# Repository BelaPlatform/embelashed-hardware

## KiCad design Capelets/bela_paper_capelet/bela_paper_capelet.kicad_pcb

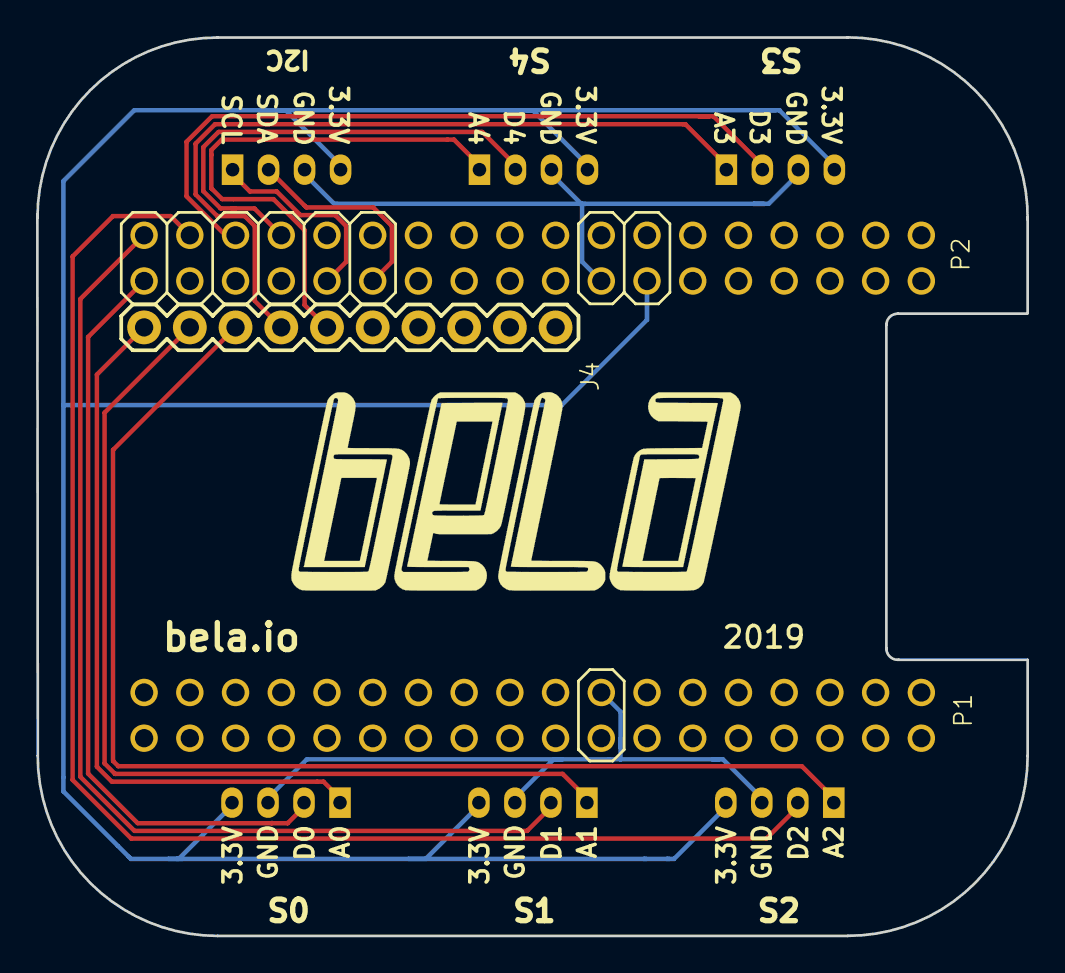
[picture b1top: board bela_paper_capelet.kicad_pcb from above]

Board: 2 copper layers, 55.0 x 49.9 mm, 9 parts (0 on the bottom side), 14 nets.

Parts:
J1, J2, J3, J5, J6, J7: Grove_4x2mm; JST_PH_S4B-PH-K_04x2.00mm_Angled
J4: M10SILK_FEMALE_PTH; 1X10
P1: PINHD-2X18; 2X18_P1
P2: PINHD-2X18; 2X18_P2

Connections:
+3V3: J1.4, J2.4, J3.4, J5.4, J6.4, J7.4
/A0: J4.10, J5.1
/A1: J4.9, J6.1
/A2: J4.8, J7.1
/A3: J3.1, J4.7
/A4: J2.1, J4.6
/D0: J5.2, P2.1
/D1: J6.2, P2.2
/D2: J7.2, P2.4
/D3: J3.2, P2.6
/D4: J2.2, P2.8
/SCL: J1.1, P2.9
/SDA: J1.2, P2.11
GND: J1.3, J2.3, J3.3, J4.2, J5.3, J6.3, J7.3, P1.16, P1.22, P2.15, P2.21

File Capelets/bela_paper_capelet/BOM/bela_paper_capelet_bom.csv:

Component Count:,9,,,,,
Individual Components:,,,,,,
Item,Qty,Reference(s),Value,Brand,Part number,Link
,,J1,Grove_4x2mm,Seeed Studio,110990037,https://uk.rs-online.com/web/p/semiconductor-development-kit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
,,J2,Grove_4x2mm,Seeed Studio,110990037,https://uk.rs-online.com/web/p/semiconductor-development-kit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
,,J3,Grove_4x2mm,Seeed Studio,110990037,https://uk.rs-online.com/web/p/semiconductor-development-kit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
,,J4,M10SILK_FEMALE_PTH,TE Connectivity,1-826648-0,https://uk.rs-online.com/web/p/pcb-headers/7189967/
,,J5,Grove_4x2mm,Seeed Studio,110990037,https://uk.rs-online.com/web/p/semiconductor-development-kit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
,,J6,Grove_4x2mm,Seeed Studio,110990037,https://uk.rs-online.com/web/p/semiconductor-development-kit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
,,J7,Grove_4x2mm,Seeed Studio,110990037,https://uk.rs-online.com/web/p/semiconductor-development-kit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
,,P1,PINHD-2X18,Molex,90131-0138,https://uk.rs-online.com/web/p/pcb-headers/6703487/
,,P2,PINHD-2X18,Molex,90131-0138,https://uk.rs-online.com/web/p/pcb-headers/6703487/
,,,,,,
Collated Components:,,,,,,
Item,Qty,Reference(s),Value,,Part number,Link
1,6,"J1, J2, J3, J5, J6, J7",Grove_4x2mm,Seeed Studio,110990037,https://uk.rs-online.com/web/p/semiconductor-development-kit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
2,1,J4,M10SILK_FEMALE_PTH,TE Connectivity,1-826648-0,https://uk.rs-online.com/web/p/pcb-headers/7189967/
3,2,"P1, P2",PINHD-2X18,Molex,90131-0138,https://uk.rs-online.com/web/p/pcb-headers/6703487/

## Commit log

2019-05-30 Added Kicad files for capelets and connectors
